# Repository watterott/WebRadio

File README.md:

# ARM Cortex-M3 WebRadio
The ARM WebRadio is an embedded Internet Radio based on an ARM Cortex-M3 Microcontroller and VS1053 Audio Codec.
The VS1053 can decode various audio formats, including Ogg Vorbis, MP3, AAC, WMA, FLAC, WAV, MIDI.

## Features
* Open-Source Hardware
  * Microcontroller: LM3S6950 ARM Cortex-M3 from Luminary Micro / TI
  * Audio Codec: VS1053 from VLSI
  * Display: S65 LCD with 176x132 pixel and 16bit color
  * microSD Socket
  * Rotary Encoder
  * IR Receiver (RC5)
  * PoE (Power over Ethernet)
* Open-Source Software
  * Play Shoutcast/Icecast and RTSP Streams
  * Play audio files from the memory card
  * Alarm Clock

## Hardware and Software
* 
* [Schematics + Layout](https://github.com/watterott/WebRadio/tree/master/hardware)
* [Software/Firmware](https://github.com/watterott/WebRadio/tree/master/software)

## Videos
* [ARM WebRadio test buildup](http://www.youtube.com/watch?v=d3AU1xSci-s)
* [ARM WebRadio v1 prototype](http://www.youtube.com/watch?v=I5wxE6ul4LM)
* [ARM WebRadio v2 demo board](http://www.youtube.com/watch?v=boI7PvBz0HM)
* [ARM WebRadio v3](http://www.youtube.com/watch?v=70_Qk82P8Xw)

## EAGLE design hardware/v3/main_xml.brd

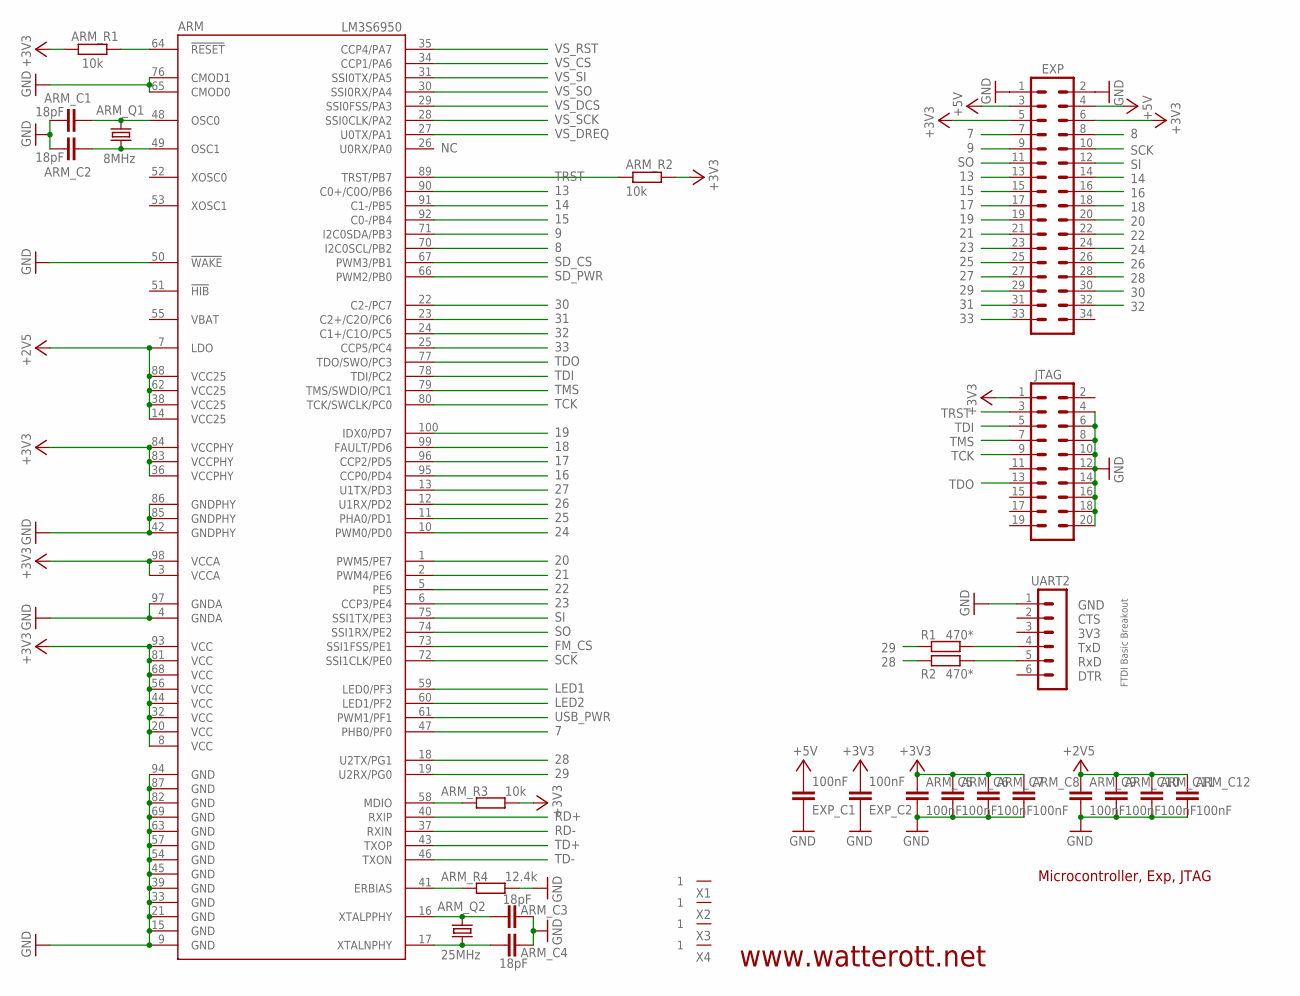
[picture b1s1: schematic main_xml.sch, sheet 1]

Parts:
ARM: LM3S6950; LQFP100
ARM_C1, ARM_C2, ARM_C3, ARM_C4: 18pF; C0603
ARM_C5, ARM_C6, ARM_C7, ARM_C8, ARM_C9, ARM_C10, ARM_C11, ARM_C12: 100nF; C0603
ARM_Q1: 8MHz; CS10
ARM_Q2: 25MHz; CS10
ARM_R1, ARM_R2, ARM_R3: 10k; R0603
ARM_R4: 12.4k; R0603
EXP: MA17-2
EXP_C1, EXP_C2: 100nF; C0603
JTAG: MA10-2SMD; MA10-2_SMD
R1, R2: 470*; R0603
UART2: MA06-1
X1, X2, X3, X4: ELLIPTICAL-PADS; SMD-ELLIPSE

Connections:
7: ARM.47 (PHB0/PF0), EXP.7
8: ARM.70 (I2C0SCL/PB2), EXP.8
9: ARM.71 (I2C0SDA/PB3), EXP.9
13: ARM.90 (C0+/C0O/PB6), EXP.13
14: ARM.91 (C1-/PB5), EXP.14
15: ARM.92 (C0-/PB4), EXP.15
16: ARM.95 (CCP0/PD4), EXP.16
17: ARM.96 (CCP2/PD5), EXP.17
18: ARM.99 (FAULT/PD6), EXP.18
19: ARM.100 (IDX0/PD7), EXP.19
20: ARM.1 (PWM5/PE7), EXP.20
21: ARM.2 (PWM4/PE6), EXP.21
22: ARM.5 (PE5), EXP.22
23: ARM.6 (CCP3/PE4), EXP.23
24: ARM.10 (PWM0/PD0), EXP.24
25: ARM.11 (PHA0/PD1), EXP.25
26: ARM.12 (U1RX/PD2), EXP.26
27: ARM.13 (U1TX/PD3), EXP.27
28: ARM.18 (U2TX/PG1), EXP.28, R2.1
29: ARM.19 (U2RX/PG0), EXP.29, R1.1
30: ARM.22 (C2-/PC7), EXP.30
31: ARM.23 (C2+/C2O/PC6), EXP.31
32: ARM.24 (C1+/C1O/PC5), EXP.32
33: ARM.25 (CCP5/PC4), EXP.33
+2V5: ARM.7 (LDO), ARM.14 (VCC25), ARM.38 (VCC25), ARM.62 (VCC25), ARM.88 (VCC25), ARM_C9.1, ARM_C10.1, ARM_C11.1, ARM_C12.1
+3V3: ARM.3 (VCCA), ARM.8 (VCC), ARM.20 (VCC), ARM.32 (VCC), ARM.36 (VCCPHY), ARM.44 (VCC), ARM.56 (VCC), ARM.68 (VCC), ARM.81 (VCC), ARM.83 (VCCPHY), ARM.84 (VCCPHY), ARM.93 (VCC), ARM.98 (VCCA), ARM_C5.1, ARM_C6.1, ARM_C7.1, ARM_C8.1, ARM_R1.1, ARM_R2.2, ARM_R3.2, EXP.5, EXP.6, EXP_C2.2, JTAG.1; also elsewhere on the board
+5V: EXP.3, EXP.4, EXP_C1.2; also elsewhere on the board
ERBIAS: ARM.41 (ERBIAS), ARM_R4.1
FM_CS: ARM.73 (SSI1FSS/PE1); also elsewhere on the board
GND: ARM.4 (GNDA), ARM.9 (GND), ARM.15 (GND), ARM.21 (GND), ARM.33 (GND), ARM.39 (GND), ARM.42 (GNDPHY), ARM.45 (GND), ARM.50 (!WAKE), ARM.54 (GND), ARM.57 (GND), ARM.63 (GND), ARM.65 (CMOD0), ARM.69 (GND), ARM.76 (CMOD1), ARM.82 (GND), ARM.85 (GNDPHY), ARM.86 (GNDPHY), ARM.87 (GND), ARM.94 (GND), ARM.97 (GNDA), ARM_C1.2, ARM_C2.2, ARM_C3.2, ARM_C4.2, ARM_C5.2, ARM_C6.2, ARM_C7.2, ARM_C8.2, ARM_C9.2, ARM_C10.2, ARM_C11.2, ARM_C12.2, ARM_R4.2, EXP.1, EXP.2, EXP_C1.1, EXP_C2.1, JTAG.4, JTAG.6, JTAG.8, JTAG.10, JTAG.12, JTAG.14, JTAG.16, JTAG.18, JTAG.20, UART2.1; also elsewhere on the board
LED1: ARM.59 (LED0/PF3); also elsewhere on the board
LED2: ARM.60 (LED1/PF2); also elsewhere on the board
MDIO: ARM.58 (MDIO), ARM_R3.1
unnamed: ARM.48 (OSC0), ARM_C1.1, ARM_Q1.2
unnamed: ARM.49 (OSC1), ARM_C2.1, ARM_Q1.1
unnamed: ARM.17 (XTALNPHY), ARM_C4.1, ARM_Q2.1
unnamed: ARM.16 (XTALPPHY), ARM_C3.1, ARM_Q2.2
RD+: ARM.40 (RXIP); also elsewhere on the board
RD-: ARM.37 (RXIN); also elsewhere on the board
RESET: ARM.64 (!RESET), ARM_R1.2
RXD: R2.2, UART2.5
SCK: ARM.72 (SSI1CLK/PE0), EXP.10; also elsewhere on the board
SD_CS: ARM.67 (PWM3/PB1); also elsewhere on the board
SD_PWR: ARM.66 (PWM2/PB0); also elsewhere on the board
SI: ARM.75 (SSI1TX/PE3), EXP.12; also elsewhere on the board
SO: ARM.74 (SSI1RX/PE2), EXP.11; also elsewhere on the board
TCK: ARM.80 (TCK/SWCLK/PC0), JTAG.9
TD+: ARM.43 (TXOP); also elsewhere on the board
TD-: ARM.46 (TXON); also elsewhere on the board
TDI: ARM.78 (TDI/PC2), JTAG.5
TDO: ARM.77 (TDO/SWO/PC3), JTAG.13
TMS: ARM.79 (TMS/SWDIO/PC1), JTAG.7
TRST: ARM.89 (TRST/PB7), ARM_R2.1, JTAG.3
TXD: R1.2, UART2.4
USB_PWR: ARM.61 (PWM1/PF1); also elsewhere on the board
VBAT: ARM.55 (VBAT)
VS_CS: ARM.34 (CCP1/PA6); also elsewhere on the board
VS_DCS: ARM.29 (SSI0FSS/PA3); also elsewhere on the board
VS_DREQ: ARM.27 (U0TX/PA1); also elsewhere on the board
VS_RST: ARM.35 (CCP4/PA7); also elsewhere on the board
VS_SCK: ARM.28 (SSI0CLK/PA2); also elsewhere on the board
VS_SI: ARM.31 (SSI0TX/PA5); also elsewhere on the board
VS_SO: ARM.30 (SSI0RX/PA4); also elsewhere on the board

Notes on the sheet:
Microcontroller, Exp, JTAG
www.watterott.net
CTS
3V3
GND
TxD
RxD
DTR
FTDI Basic Breakout

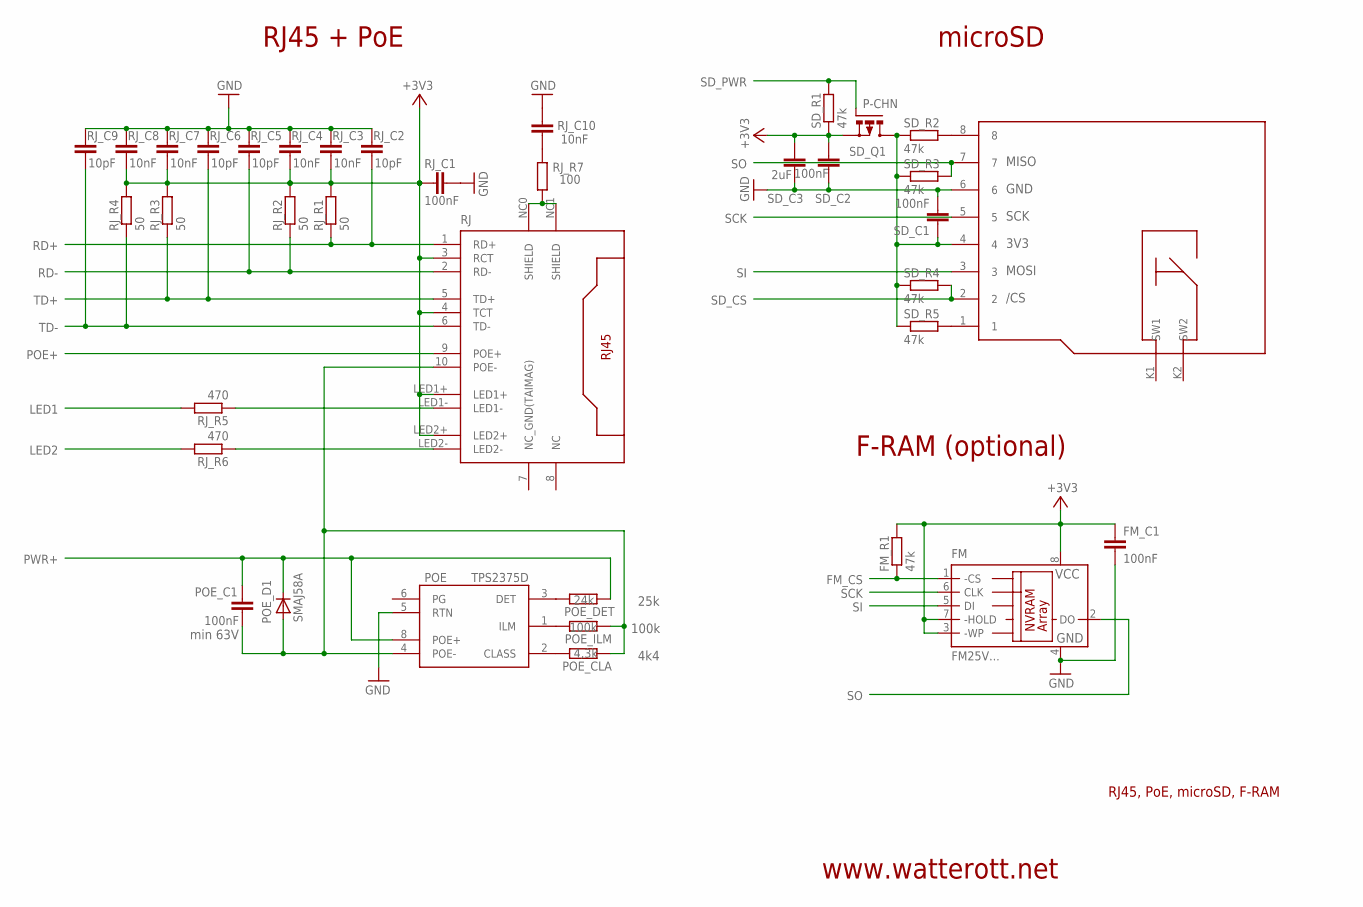
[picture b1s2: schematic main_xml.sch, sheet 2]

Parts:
FM: FM25V...; SO8
FM_C1: 100nF; C0603
FM_R1: 47k; R0603
POE: TPS2375D; SO08
POE_C1: 100nF; C1206; VOLTAGE min 63V
POE_CLA: 4,3k; R0603
POE_D1: SMAJ58A; DO214AA
POE_DET: 24k; R0603
POE_ILM: 100k; R0603
RJ: RJ45-8-POEWE; WE_POE
RJ_C1: 100nF; C0603
RJ_C2, RJ_C5, RJ_C6, RJ_C9: 10pF; C0603
RJ_C3, RJ_C4, RJ_C7, RJ_C8, RJ_C10: 10nF; C0603
RJ_R1, RJ_R2, RJ_R3, RJ_R4: 50; R0603
RJ_R5, RJ_R6: 470; R0603
RJ_R7: 100; R0603
SD: MICRO-SD
SD_C1, SD_C2: 100nF; C0603
SD_C3: 2uF; C0603
SD_Q1: P-CHN; MICRO3
SD_R1, SD_R2, SD_R3, SD_R4, SD_R5: 47k; R0603

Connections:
+3V3: FM.3 (-WP), FM.7 (-HOLD), FM.8 (VCC), FM_C1.1, FM_R1.2, RJ.3 (RCT), RJ.4 (TCT), RJ.LED1+, RJ.LED2+, RJ_C1.1, RJ_C3.2, RJ_C4.2, RJ_C7.2, RJ_C8.2, RJ_R1.2, RJ_R2.2, RJ_R3.2, RJ_R4.2, SD_C2.2, SD_C3.2, SD_Q1.2 (S), SD_R1.1; also elsewhere on the board
CLASS: POE.2 (CLASS), POE_CLA.2
DET: POE.3 (DET), POE_DET.2
FM_CS: FM.1 (-CS), FM_R1.1; also elsewhere on the board
GND: FM.4 (GND), FM_C1.2, POE.5 (RTN), RJ_C1.2, RJ_C2.1, RJ_C3.1, RJ_C4.1, RJ_C5.1, RJ_C6.1, RJ_C7.1, RJ_C8.1, RJ_C9.1, RJ_C10.2, SD.6, SD_C1.2, SD_C2.1, SD_C3.1; also elsewhere on the board
ILM: POE.1 (ILM), POE_ILM.2
LED1: RJ_R5.2; also elsewhere on the board
LED2: RJ_R6.2; also elsewhere on the board
unnamed: RJ.LED2-, RJ_R6.1
unnamed: RJ.LED1-, RJ_R5.1
unnamed: RJ_C10.1, RJ_R7.1
NC: RJ.8 (NC)
NC_GND(TAIMAG): RJ.7 (NC_GND(TAIMAG))
POE+: RJ.9 (POE+); also elsewhere on the board
POE-: POE.4 (POE-), POE_C1.2, POE_CLA.1, POE_D1.A, POE_ILM.1, RJ.10 (POE-)
PWR+: POE.8 (POE+), POE_C1.1, POE_D1.C, POE_DET.1; also elsewhere on the board
RD+: RJ.1 (RD+), RJ_C2.2, RJ_R1.1; also elsewhere on the board
RD-: RJ.2 (RD-), RJ_C5.2, RJ_R2.1; also elsewhere on the board
SCK: FM.6 (CLK), SD.5; also elsewhere on the board
SD_1: SD.1, SD_R5.2
SD_3V3: SD.4, SD_C1.1, SD_Q1.3 (D), SD_R2.1, SD_R3.1, SD_R4.1, SD_R5.1
SD_8: SD.8, SD_R2.2
SD_CS: SD.2, SD_R4.2; also elsewhere on the board
SD_PWR: SD_Q1.1 (G), SD_R1.2; also elsewhere on the board
SHIELD: RJ.NC0 (SHIELD), RJ.NC1 (SHIELD), RJ_R7.2
SI: FM.5 (DI), SD.3; also elsewhere on the board
SO: FM.2 (DO), SD.7, SD_R3.2; also elsewhere on the board
TD+: RJ.5 (TD+), RJ_C6.2, RJ_R3.1; also elsewhere on the board
TD-: RJ.6 (TD-), RJ_C9.2, RJ_R4.1; also elsewhere on the board

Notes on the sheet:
RJ45, PoE, microSD, F-RAM
RJ45 + PoE
F-RAM (optional)
www.watterott.net
4k4
100k
25k
microSD

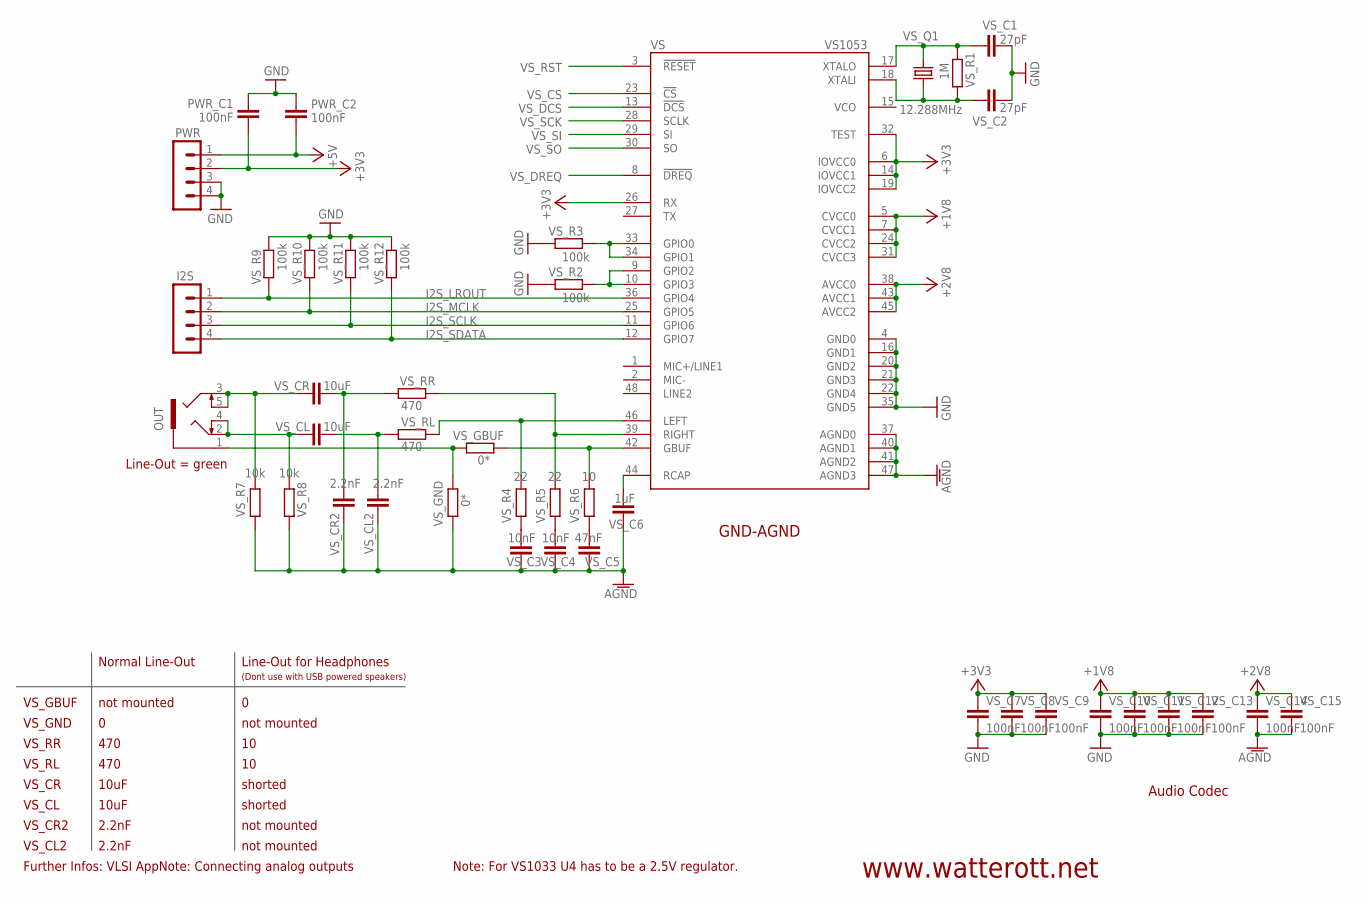
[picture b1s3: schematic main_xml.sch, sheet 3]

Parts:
I2S: MA04-1
OUT: 1503_09
PWR: MA04-1
PWR_C1, PWR_C2: 100nF; C0603
VS: VS1053; LQFP-48
VS_C1, VS_C2: 27pF; C0603
VS_C3, VS_C4: 10nF; C0603
VS_C5: 47nF; C0603
VS_C6: 1uF; C0603
VS_C7, VS_C8, VS_C9, VS_C10, VS_C11, VS_C12, VS_C13, VS_C14, VS_C15: 100nF; C0603
VS_CL: 10uF; C1210
VS_CL2: 2.2nF; C0603
VS_CR: 10uF; C1210
VS_CR2: 2.2nF; C0603
VS_GBUF: 0*; R0603
VS_GND: 0*; R0603
VS_Q1: 12.288MHz; SM49
VS_R1: 1M; R0603
VS_R2, VS_R3, VS_R9, VS_R10, VS_R11, VS_R12: 100k; R0603
VS_R4, VS_R5: 22; R0603
VS_R6: 10; R0603
VS_R7, VS_R8: 10k; R0603
VS_RL: 470; R0603
VS_RR: 470; R0603

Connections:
+1V8: VS.5 (CVCC0), VS.7 (CVCC1), VS.24 (CVCC2), VS.31 (CVCC3), VS_C10.1, VS_C11.1, VS_C12.1, VS_C13.1; also elsewhere on the board
+2V8: VS.38 (AVCC0), VS.43 (AVCC1), VS.45 (AVCC2), VS_C14.1, VS_C15.1; also elsewhere on the board
+3V3: PWR.2, PWR_C1.2, VS.6 (IOVCC0), VS.14 (IOVCC1), VS.19 (IOVCC2), VS.26 (RX), VS.32 (TEST), VS_C7.1, VS_C8.1, VS_C9.1; also elsewhere on the board
+5V: PWR.1, PWR_C2.2; also elsewhere on the board
AGND: VS.37 (AGND0), VS.40 (AGND1), VS.41 (AGND2), VS.47 (AGND3), VS_C3.1, VS_C4.1, VS_C5.1, VS_C6.1, VS_C14.2, VS_C15.2, VS_CL2.2, VS_CR2.2, VS_GND.2, VS_R7.2, VS_R8.2; also elsewhere on the board
GBUF: VS.42 (GBUF), VS_GBUF.1, VS_R6.2
GND: PWR.3, PWR.4, PWR_C1.1, PWR_C2.1, VS.4 (GND0), VS.16 (GND1), VS.20 (GND2), VS.21 (GND3), VS.22 (GND4), VS.35 (GND5), VS_C1.2, VS_C2.2, VS_C7.2, VS_C8.2, VS_C9.2, VS_C10.2, VS_C11.2, VS_C12.2, VS_C13.2, VS_R2.1, VS_R3.1, VS_R9.2, VS_R10.2, VS_R11.2, VS_R12.2; also elsewhere on the board
I2S_LROUT: I2S.1, VS.36 (GPIO4), VS_R9.1
I2S_MCLK: I2S.2, VS.25 (GPIO5), VS_R10.1
I2S_SCLK: I2S.3, VS.11 (GPIO6), VS_R11.1
I2S_SDATA: I2S.4, VS.12 (GPIO7), VS_R12.1
LEFT: VS.46 (LEFT), VS_R4.2, VS_RL.1
unnamed: VS.33 (GPIO0), VS.34 (GPIO1), VS_R3.2
unnamed: VS.9 (GPIO2), VS.10 (GPIO3), VS_R2.2
unnamed: VS.18 (XTALI), VS_C2.1, VS_Q1.1, VS_R1.2
unnamed: VS.17 (XTALO), VS_C1.1, VS_Q1.2, VS_R1.1
unnamed: OUT.1, VS_GBUF.2, VS_GND.1
unnamed: OUT.3, OUT.5, VS_CR.2, VS_R7.1
unnamed: OUT.2, OUT.4, VS_CL.2, VS_R8.1
unnamed: VS_CR.1, VS_CR2.1, VS_RR.2
unnamed: VS_CL.1, VS_CL2.1, VS_RL.2
unnamed: VS_C3.2, VS_R4.1
unnamed: VS_C4.2, VS_R5.1
unnamed: VS_C5.2, VS_R6.1
RCAP: VS.44 (RCAP), VS_C6.2
RIGHT: VS.39 (RIGHT), VS_R5.2, VS_RR.1
VS_CS: VS.23 (!CS); also elsewhere on the board
VS_DCS: VS.13 (!DCS); also elsewhere on the board
VS_DREQ: VS.8 (!DREQ); also elsewhere on the board
VS_RST: VS.3 (!RESET); also elsewhere on the board
VS_SCK: VS.28 (SCLK); also elsewhere on the board
VS_SI: VS.29 (SI); also elsewhere on the board
VS_SO: VS.30 (SO); also elsewhere on the board

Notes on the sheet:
Audio Codec
www.watterott.net
Normal Line-Out
Line-Out for Headphones
VS_GND
VS_GBUF
VS_RR
VS_RL
VS_CL
VS_CR
not mounted
470
10uF
shorted
VS_CR2
VS_CL2
2.2nF
Note: For VS1033 U4 has to be a 2.5V regulator.
Line-Out = green
(Dont use with USB powered speakers)
Further Infos: VLSI AppNote: Connecting analog outputs
GND-AGND

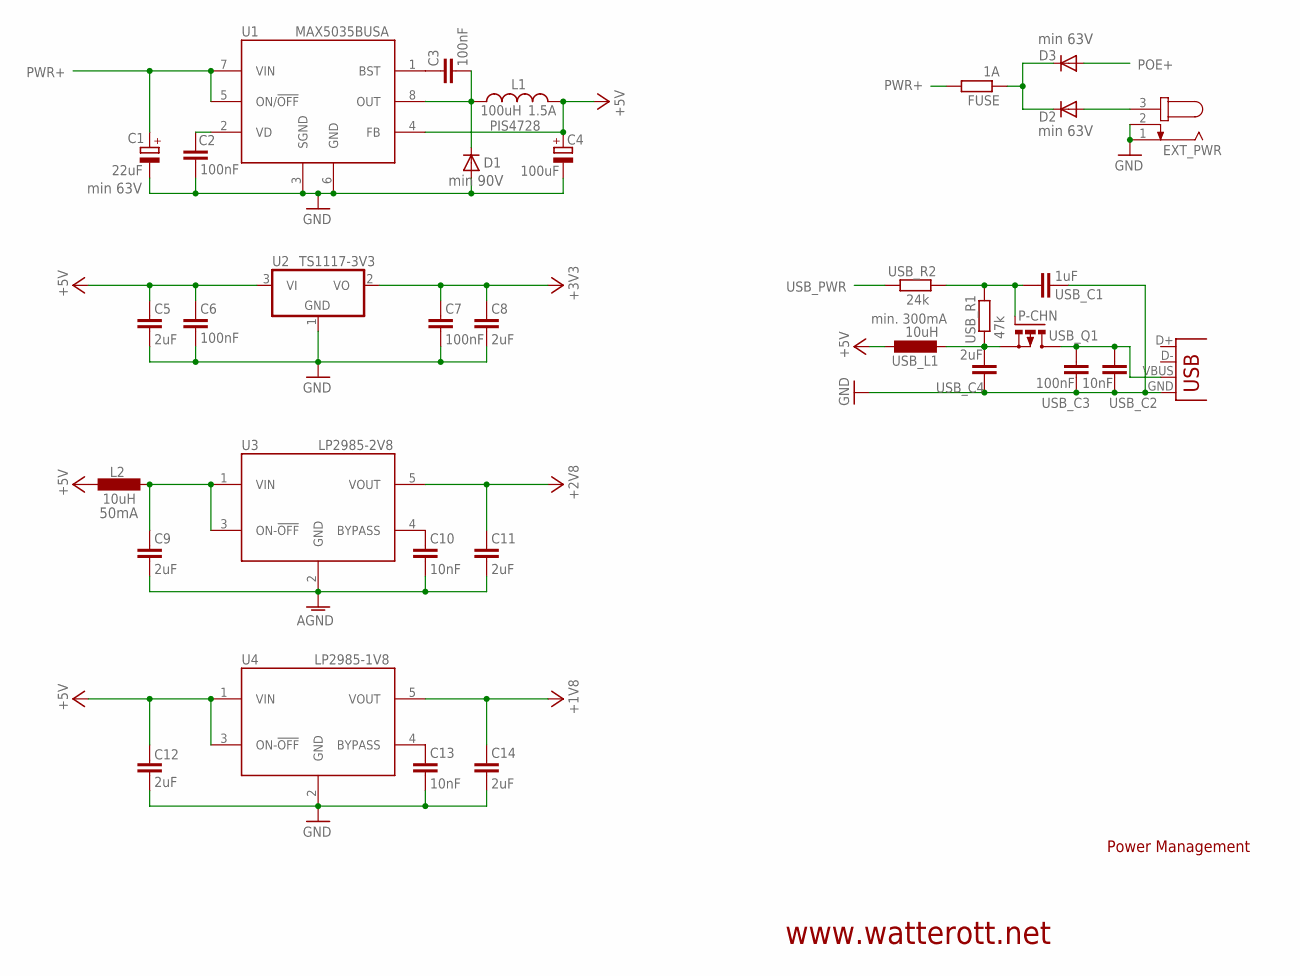
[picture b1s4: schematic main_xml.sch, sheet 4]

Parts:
C1: 22uF; 153CLV-0810; VOLTAGE min 63V
C2, C3, C6, C7: 100nF; C0603
C4: 100uF; 153CLV-0810
C5, C8, C9, C11, C12, C14: 2uF; C0603
C10, C13: 10nF; C0603
D1: DIODE-DO214AA; DO214AA; VOLTAGE min 90V
D2, D3: DIODE-DO214AA; DO214AA; VOLTAGE min 63V
EXT_PWR: JACK-PLUG0; SPC4077
FUSE: 1A; R1206
L1: 100uH; CDRH
L2: 10uH; L3230M
U1: MAX5035BUSA; SO8
U2: TS1117-3V3; SOT223
U3: LP2985-2V8; SOT23-5
U4: LP2985-1V8; SOT23-5
USB: USB-A-S
USB_C1: 1uF; C0603
USB_C2: 10nF; C0603
USB_C3: 100nF; C0603
USB_C4: 2uF; C0805
USB_L1: 10uH; L3230M
USB_Q1: P-CHN; MICRO3
USB_R1: 47k; R0603
USB_R2: 24k; R0603

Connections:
5V_VIN: C9.2, L2.2, U3.1 (VIN), U3.3 (ON-!OFF)
+1V8: C14.1, U4.5 (VOUT); also elsewhere on the board
+2V8: C11.1, U3.5 (VOUT); also elsewhere on the board
+3V3: C7.1, C8.1, U2.2 (VO); also elsewhere on the board
+5V: C4.+, C5.1, C6.2, C12.2, L1.2, L2.1, U1.4 (FB), U2.3 (VI), U4.1 (VIN), U4.3 (ON-!OFF), USB_L1.1; also elsewhere on the board
AGND: C9.1, C10.2, C11.2, U3.2 (GND); also elsewhere on the board
BST: C3.1, U1.1 (BST)
GND: C1.-, C2.2, C4.-, C5.2, C6.1, C7.2, C8.2, C12.1, C13.2, C14.2, D1.A, EXT_PWR.1, EXT_PWR.2, U1.3 (SGND), U1.6 (GND), U2.1 (GND), U4.2 (GND), USB.GND, USB_C1.1, USB_C2.2, USB_C3.2, USB_C4.1; also elsewhere on the board
unnamed: USB_C4.2, USB_L1.2, USB_Q1.2 (S), USB_R1.1
unnamed: USB.VBUS, USB_C2.1, USB_C3.1, USB_Q1.3 (D)
unnamed: USB_C1.2, USB_Q1.1 (G), USB_R1.2, USB_R2.1
unnamed: D2.A, EXT_PWR.3
unnamed: D2.C, D3.C, FUSE.1
unnamed: C10.1, U3.4 (BYPASS)
unnamed: C13.1, U4.4 (BYPASS)
OUT: C3.2, D1.C, L1.1, U1.8 (OUT)
POE+: D3.A; also elsewhere on the board
PWR+: C1.+, FUSE.2, U1.5 (ON/!OFF), U1.7 (VIN); also elsewhere on the board
USB_PWR: USB_R2.2; also elsewhere on the board
VD: C2.1, U1.2 (VD)

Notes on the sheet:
Power Management
www.watterott.net
1.5A
PIS4728

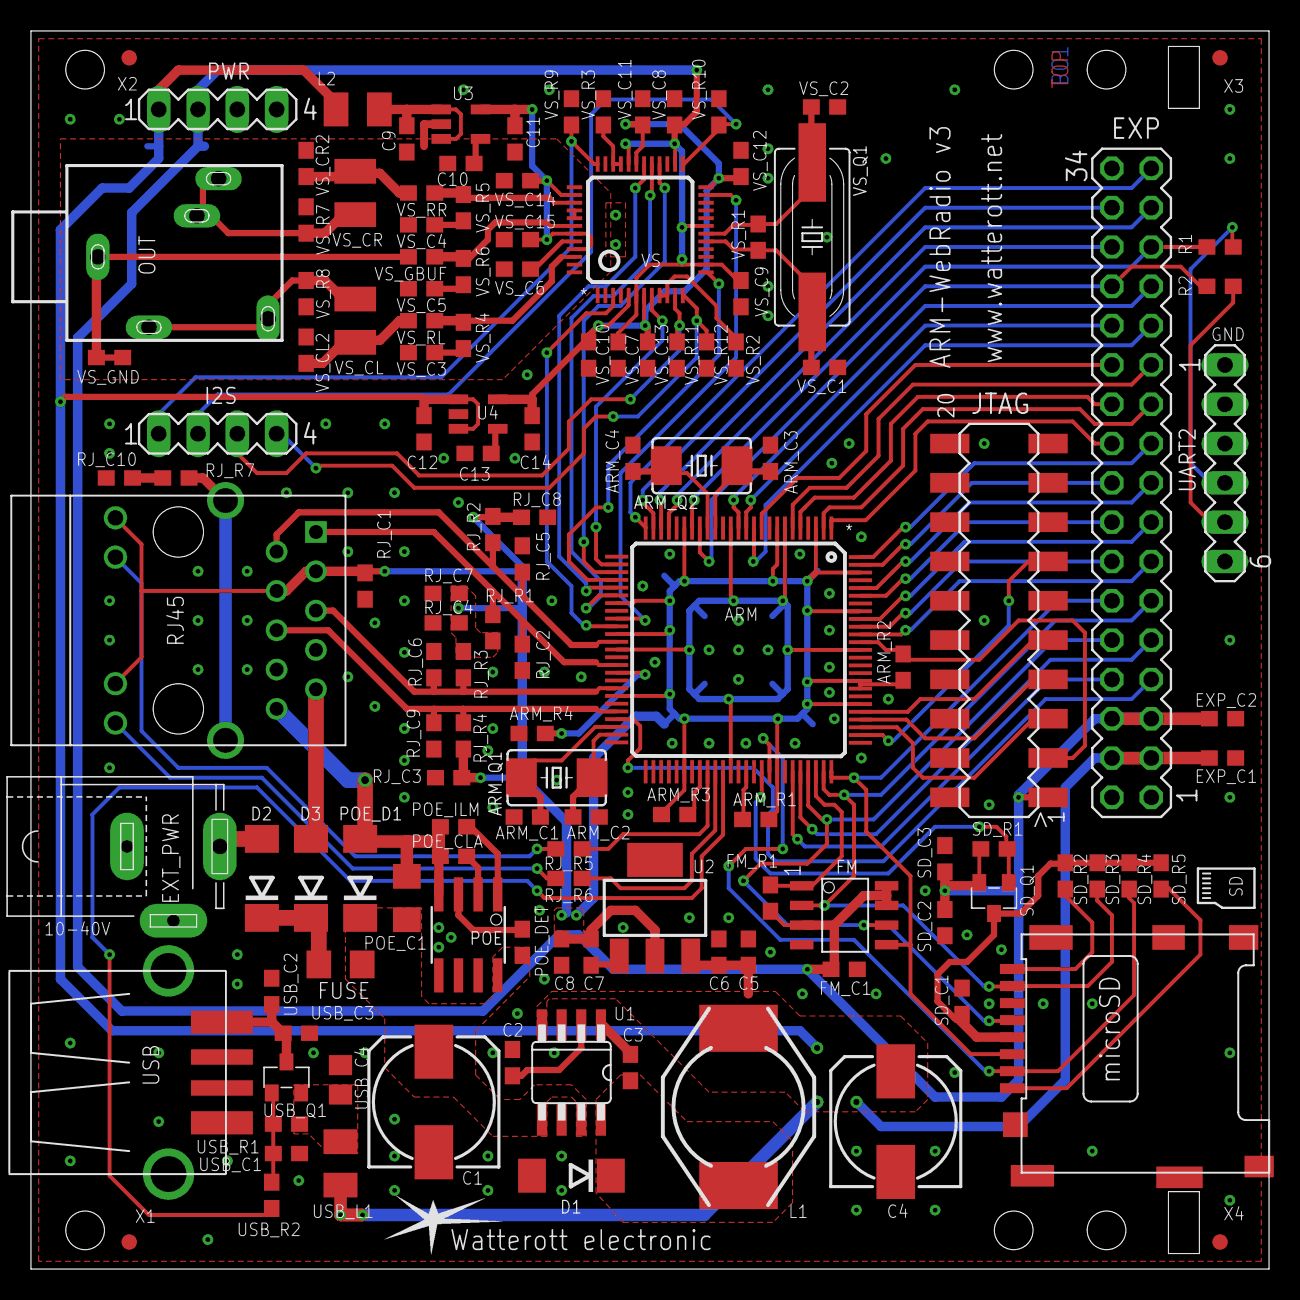
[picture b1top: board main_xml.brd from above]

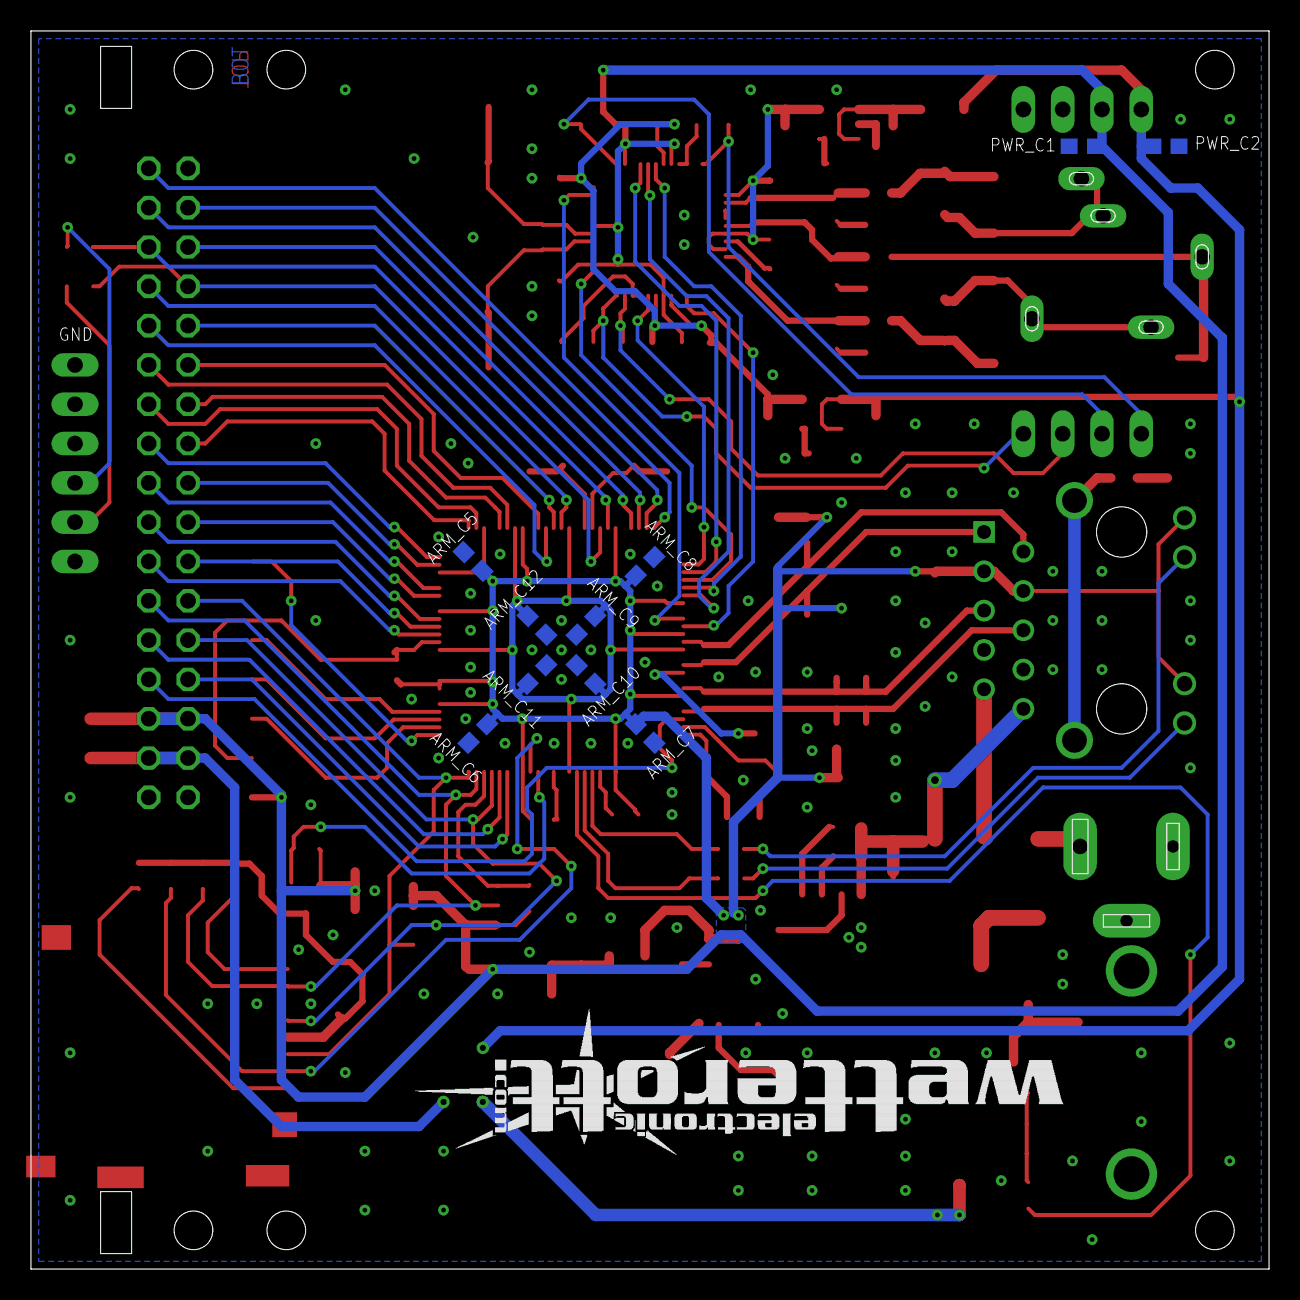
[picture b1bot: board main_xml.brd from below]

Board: 2 copper layers, 80.0 x 80.0 mm, 143 parts (10 on the bottom side), 109 nets.

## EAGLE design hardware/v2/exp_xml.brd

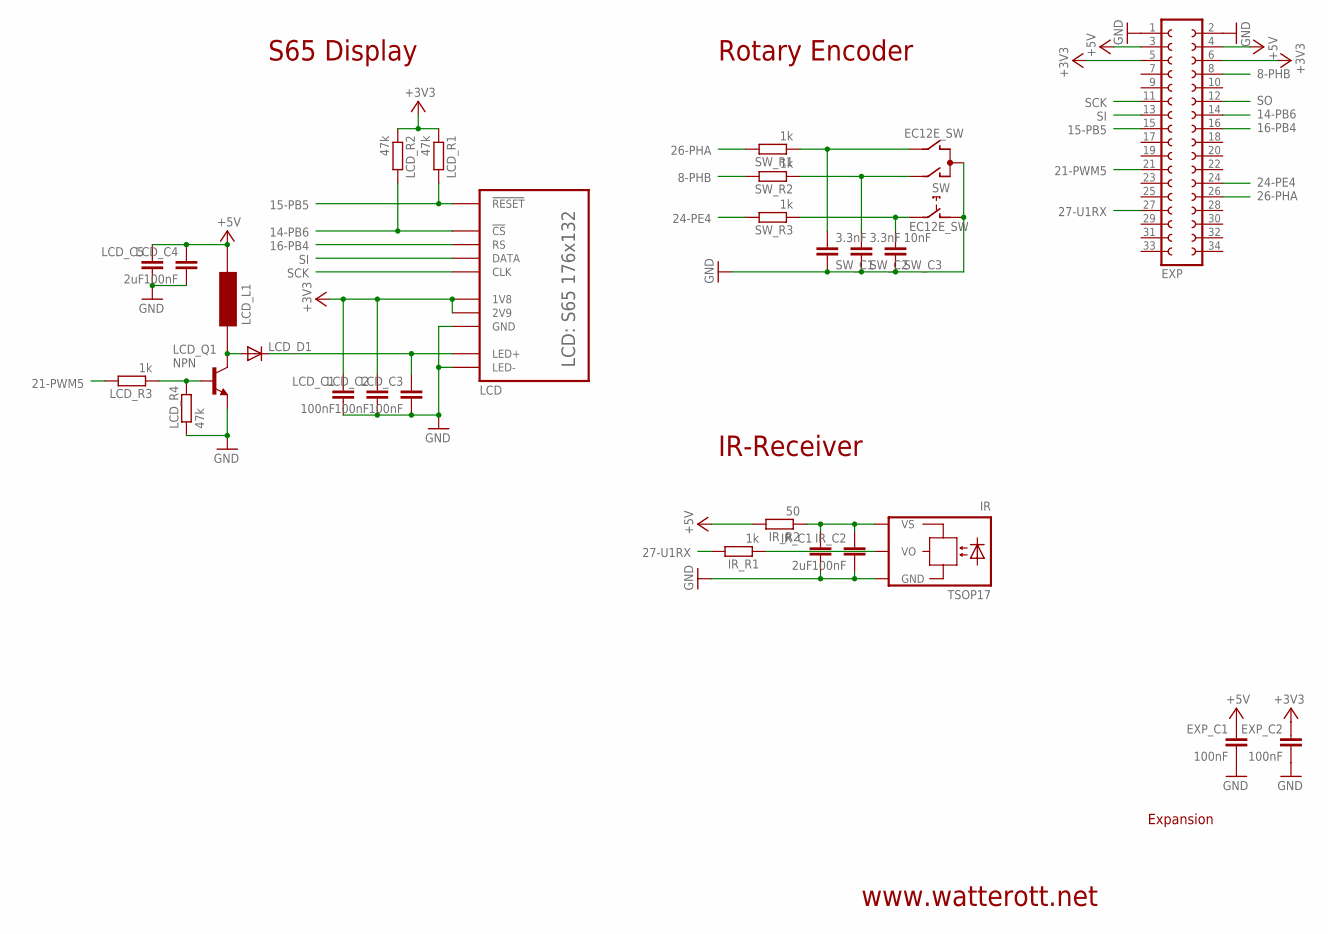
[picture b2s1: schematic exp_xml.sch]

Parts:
EXP: FE17-2SMD; FE17-2_SMD
EXP_C1, EXP_C2: 100nF; C0603
IR: TSOP17
IR_C1: 2uF; C0603
IR_C2: 100nF; C0603
IR_R1: 1k; R0603
IR_R2: 50; R0603
LCD: S65
LCD_C1, LCD_C2, LCD_C3: 100nF; C0603
LCD_C4: 100nF; C0805
LCD_C5: 2uF; C0805
LCD_D1: Schottky; DO214AA
LCD_L1: 2mH; WE-PD3-S
LCD_Q1: NPN; SOT23
LCD_R1, LCD_R2, LCD_R4: 47k; R0603
LCD_R3: 1k; R0603
SW: EC12E_SW; ALPS_EC12E_SW
SW_C1, SW_C2: 3.3nF; C0603
SW_C3: 10nF; C0603
SW_R1, SW_R2, SW_R3: 1k; R0603

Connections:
8-PHB: EXP.8, SW_R2.2
14-PB6: EXP.14, LCD.CS (!CS), LCD_R2.2
15-PB5: EXP.15, LCD.RESET (!RESET), LCD_R1.2
16-PB4: EXP.16, LCD.RS
21-PWM5: EXP.21, LCD_R3.2
21-PWM523: LCD_Q1.1 (B), LCD_R3.1, LCD_R4.2
24-PE4: EXP.24, SW_R3.2
26-PHA: EXP.26, SW_R1.2
27-U1RX: EXP.27, IR_R1.2
+3V3: EXP.5, EXP.6, EXP_C2.1, LCD.1V8, LCD.2V9, LCD_C1.1, LCD_C2.1, LCD_R1.1, LCD_R2.1
+5V: EXP.3, EXP.4, EXP_C1.1, IR_R2.2, LCD_C4.1, LCD_C5.1, LCD_L1.P$2
GND: EXP.1, EXP.2, EXP_C1.2, EXP_C2.2, IR.GND, IR_C1.2, IR_C2.2, LCD.GND, LCD.LED-, LCD_C1.2, LCD_C2.2, LCD_C3.2, LCD_C4.2, LCD_C5.2, LCD_Q1.2 (E), LCD_R4.1, SW.C, SW.D (1), SW_C1.1, SW_C2.1, SW_C3.1
LED+: LCD.LED+, LCD_C3.1, LCD_D1.C
unnamed: SW.B, SW_C1.2, SW_R1.1
unnamed: LCD_D1.A, LCD_L1.P$1, LCD_Q1.3 (C)
unnamed: SW.A, SW_C2.2, SW_R2.1
unnamed: SW.E (2), SW_C3.2, SW_R3.1
SCK: EXP.11, LCD.CLK
SI: EXP.13, LCD.DATA
SO: EXP.12
VO: IR.VO, IR_R1.1
VS: IR.VS, IR_C1.1, IR_C2.1, IR_R2.1

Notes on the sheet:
S65 Display
Rotary Encoder
IR-Receiver
Expansion
www.watterott.net

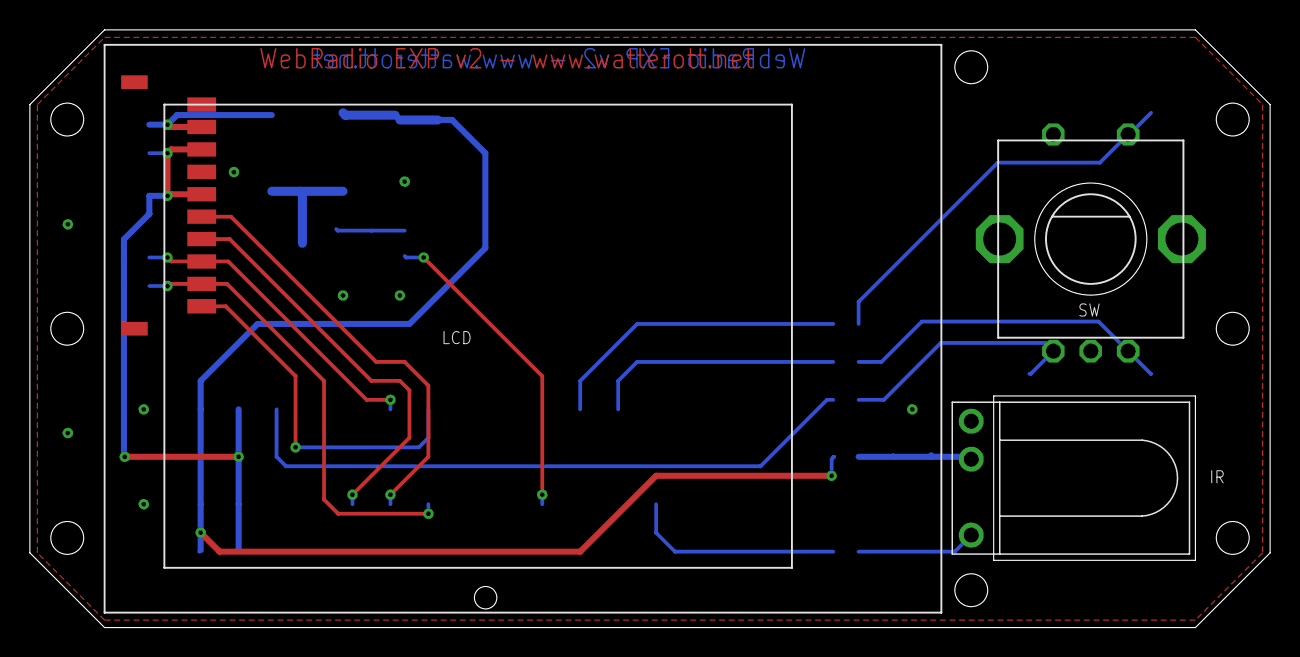
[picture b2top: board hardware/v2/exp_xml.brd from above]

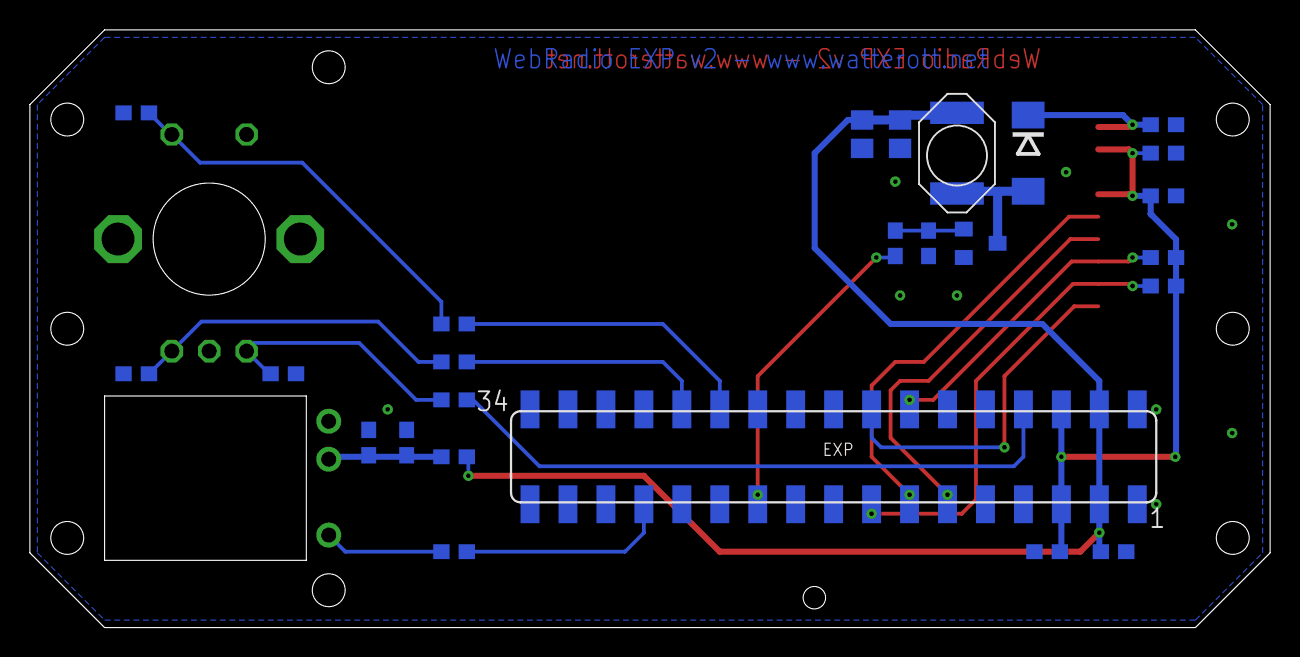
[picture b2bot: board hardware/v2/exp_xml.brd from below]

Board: 2 copper layers, 83.0 x 40.0 mm, 28 parts (25 on the bottom side), 21 nets.

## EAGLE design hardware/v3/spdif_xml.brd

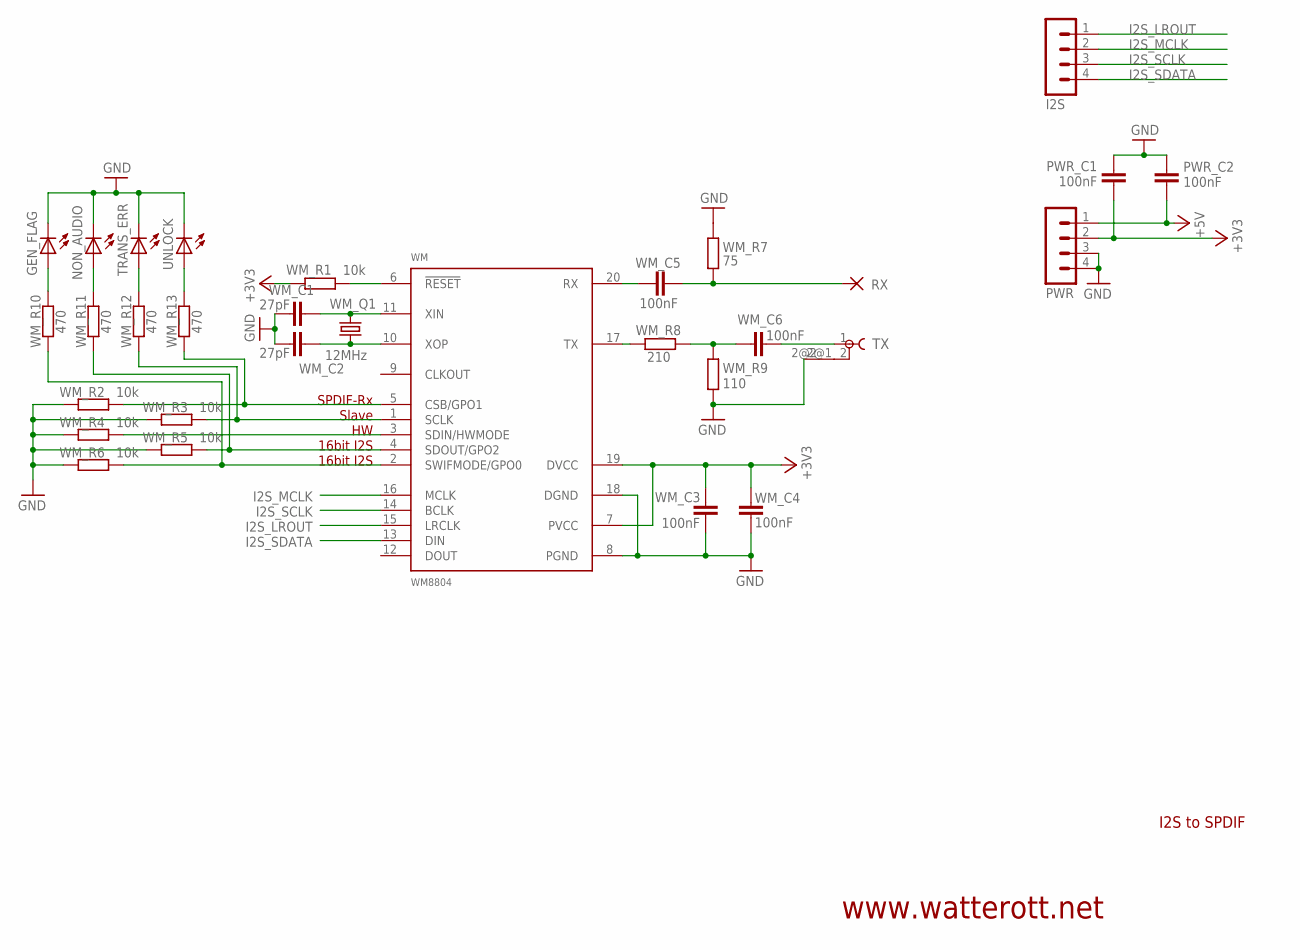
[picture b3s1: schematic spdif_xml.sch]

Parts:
GEN_FLAG: LEDCHIPLED_0805; CHIPLED_0805
I2S: MA04-1
NON_AUDIO: LEDCHIPLED_0805; CHIPLED_0805
PWR: MA04-1
PWR_C1, PWR_C2: 100nF; C0603
RX: WIREPAD1,6/0,8; 1,6/0,8
TRANS_ERR: LEDCHIPLED_0805; CHIPLED_0805
TX: TOBU3
UNLOCK: LEDCHIPLED_0805; CHIPLED_0805
WM: WM8804; TSSOP20
WM_C1, WM_C2: 27pF; C0603
WM_C3, WM_C4, WM_C5, WM_C6: 100nF; C0603
WM_Q1: 12MHz; HC49UP
WM_R1, WM_R2, WM_R3, WM_R4, WM_R5, WM_R6: 10k; R0603
WM_R7: 75; R0603
WM_R8: 210; R0603
WM_R9: 110; R0603
WM_R10, WM_R11, WM_R12, WM_R13: 470; R0603

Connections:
+3V3: PWR.2, PWR_C1.2, WM.7 (PVCC), WM.19 (DVCC), WM_C3.1, WM_C4.1, WM_R1.1
+5V: PWR.1, PWR_C2.2
CSB: WM.5 (CSB/GPO1), WM_R2.2, WM_R13.1
GEN_FLAG: GEN_FLAG.A, WM_R10.2
GND: GEN_FLAG.C, NON_AUDIO.C, PWR.3, PWR.4, PWR_C1.1, PWR_C2.1, TRANS_ERR.C, TX.2@2 (4), UNLOCK.C, WM.8 (PGND), WM.18 (DGND), WM_C1.2, WM_C2.2, WM_C3.2, WM_C4.2, WM_R2.1, WM_R3.1, WM_R4.1, WM_R5.1, WM_R6.1, WM_R7.2, WM_R9.1
I2S_LROUT: I2S.1, WM.15 (LRCLK)
I2S_MCLK: I2S.2, WM.16 (MCLK)
I2S_SCLK: I2S.3, WM.14 (BCLK)
I2S_SDATA: I2S.4, WM.13 (DIN)
NON_AUDIO: NON_AUDIO.A, WM_R11.2
RESET: WM.6 (!RESET), WM_R1.2
RX0: WM.20 (RX), WM_C5.2
RX1: RX.1, WM_C5.1, WM_R7.1
SCLK: WM.1 (SCLK), WM_R3.2, WM_R12.1
SDIN: WM.3 (SDIN/HWMODE), WM_R4.2
SDOUT: WM.4 (SDOUT/GPO2), WM_R5.2, WM_R11.1
SWIFMODE: WM.2 (SWIFMODE/GPO0), WM_R6.2, WM_R10.1
TRANS_ERR: TRANS_ERR.A, WM_R12.2
TX0: WM.17 (TX), WM_R8.1
TX1: WM_C6.2, WM_R8.2, WM_R9.2
TX2: TX.1, WM_C6.1
UNLOCK: UNLOCK.A, WM_R13.2
XIN: WM.11 (XIN), WM_C1.1, WM_Q1.2
XOP: WM.10 (XOP), WM_C2.1, WM_Q1.1

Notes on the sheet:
I2S to SPDIF
www.watterott.net
Slave
SPDIF-Rx
16bit I2S

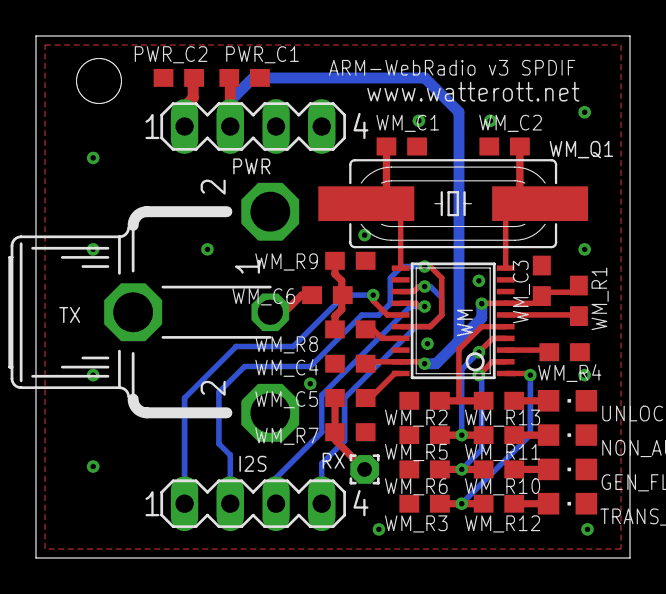
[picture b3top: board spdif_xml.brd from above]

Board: 2 copper layers, 33.0 x 29.0 mm, 31 parts (0 on the bottom side), 24 nets.
